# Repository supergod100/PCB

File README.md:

# KiCADでPCB作成
- main: PCB基板を作成するためのフォルダ・ファイル。完成形になるもの
- symbols: nRF52840_BLE_MCUの回路図等
- footprints: nRF52840_BLE_MCUのフットプリント

# フォルダ構成
```
Documents/KiCad/9.0/
    ├── footprints
    │   └── Original.pretty
    │       └── nRF52840_BLE_MCU.kicad_mod
    ├── main
    │   ├── fp-info-cache
    │   ├── main
    │   ├── main.kicad_pcb
    │   ├── main.kicad_prl
    │   ├── main.kicad_pro
    │   └── main.kicad_sch
    └── symbols
        ├── Original.bak
        └── Original.kicad_sym
```

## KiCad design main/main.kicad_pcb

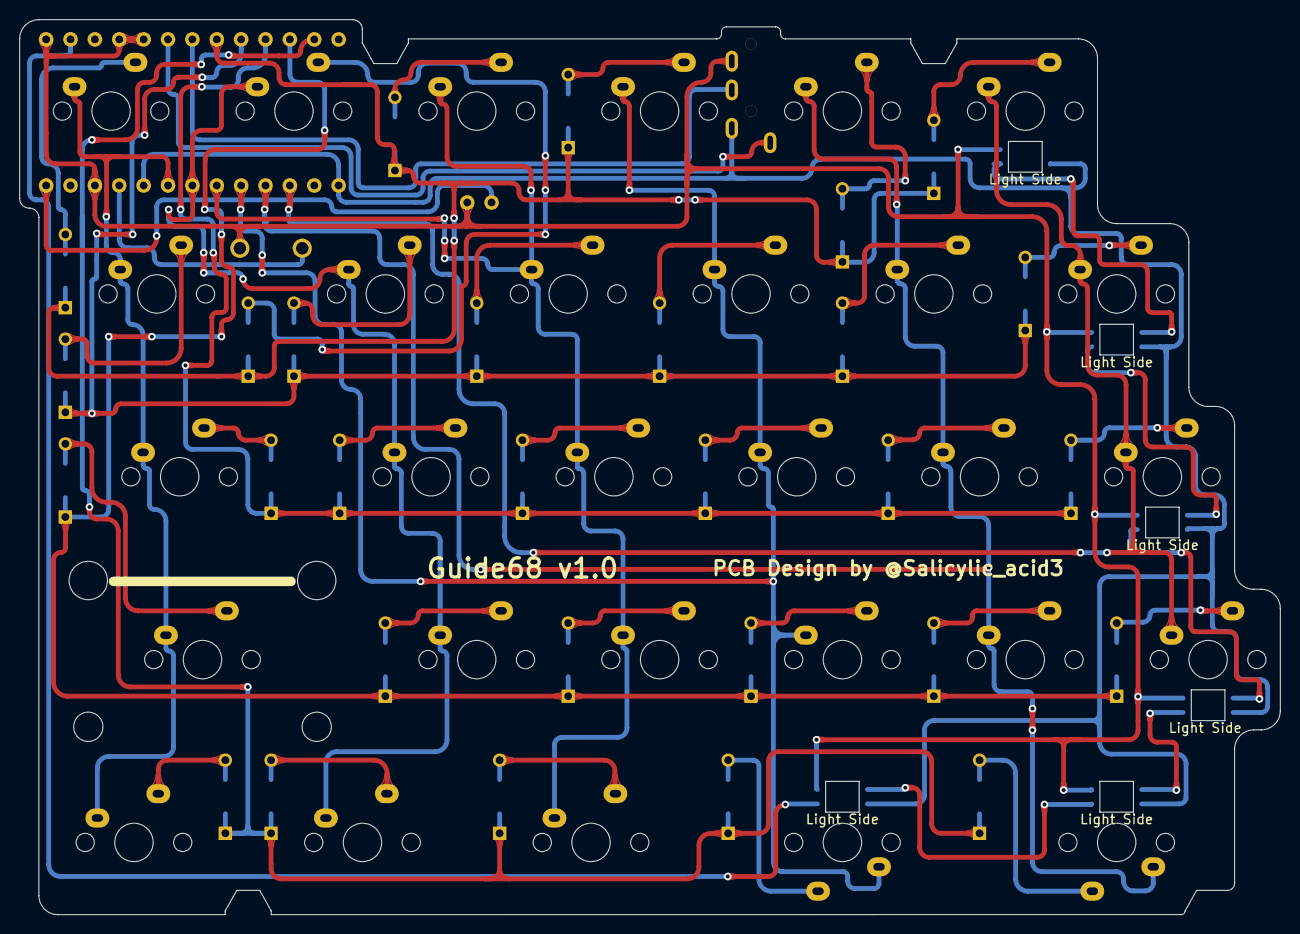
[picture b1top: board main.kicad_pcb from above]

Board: 2 copper layers, 131.3 x 93.2 mm, 68 parts (1 on the bottom side), 52 nets.

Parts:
D1, D2, D3, D4, D5, D6, D7, D8, D9, D10, D11, D12, D13, D14, D15, D16, D17, D18, D19, D20, D21, D22, D23, D24, D25, D26, D27, D28, D29: D; Diode_TH_SMD
J1: MJ-4PP-9; TRRS_MJ-4PP-9
J2: Conn_01x02; Battery_BMP_2pin
L1, L2, L3, L4, L5, L6: SK6812MINI; LED_SK6812MINI-E_BL
SW1, SW6, SW7, SW8, SW9, SW11, SW12, SW13, SW14, SW16, SW17, SW18, SW19, SW21, SW22, SW23, SW24, SW26, SW27, SW28, SW29: SW_PUSH; CherryMX_Solder_1u
SW2, SW20, SW25: SW_PUSH; CherryMX_Solder_1.5u
SW3: SW_PUSH; CherryMX_Solder_1.75u
SW4: SW_PUSH; CherryMX_Solder_2u_Rev
SW5, SW10, SW15: SW_PUSH; CherryMX_Solder_1.25u
SW30: SW_PUSH; ResetSW
U1: BLEMicroPro; Micon_BMP_7sKB

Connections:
Bat+: J2.1, U1.25 (BAT+)
Col0: SW1.1, SW2.1, SW3.1, SW4.1, SW5.1, U1.20 (F4/PIN20)
Col1: SW6.1, SW7.1, SW8.1, SW9.1, SW10.1, U1.19 (F5/PIN19)
Col2: SW11.1, SW12.1, SW13.1, SW14.1, SW15.1, U1.18 (F6/PIN18)
Col3: SW16.1, SW17.1, SW18.1, SW19.1, SW20.1, U1.17 (F7/PIN17)
Col4: SW21.1, SW22.1, SW23.1, SW24.1, SW25.1, U1.16 (B1/PIN16)
Col5: SW26.1, SW27.1, SW28.1, SW29.1, U1.15 (B3/PIN15)
Data_SCL: J1.C, U1.6 (D0/PIN6/SCL)
GND: J1.B, J2.2, L1.2 (VSS), L2.2 (VSS), L3.2 (VSS), L4.2 (VSS), L5.2 (VSS), L6.2 (VSS), SW30.2, U1.3 (GND), U1.4 (GND), U1.23 (GND), U1.26 (BAT-)
LED: L1.3 (DIN), U1.1 (D3/PIN1)
unnamed: D1.2 (A), SW1.2
unnamed: D2.2 (A), SW2.2
unnamed: D3.2 (A), SW3.2
unnamed: D4.2 (A), SW4.2
unnamed: D5.2 (A), SW5.2
unnamed: D6.2 (A), SW6.2
unnamed: D7.2 (A), SW7.2
unnamed: D8.2 (A), SW8.2
unnamed: D9.2 (A), SW9.2
unnamed: D10.2 (A), SW10.2
unnamed: D11.2 (A), SW11.2
unnamed: D12.2 (A), SW12.2
unnamed: D13.2 (A), SW13.2
unnamed: D14.2 (A), SW14.2
unnamed: D15.2 (A), SW15.2
unnamed: D16.2 (A), SW16.2
unnamed: D17.2 (A), SW17.2
unnamed: D18.2 (A), SW18.2
unnamed: D19.2 (A), SW19.2
unnamed: D20.2 (A), SW20.2
unnamed: D21.2 (A), SW21.2
unnamed: D22.2 (A), SW22.2
unnamed: D23.2 (A), SW23.2
unnamed: D24.2 (A), SW24.2
unnamed: D25.2 (A), SW25.2
unnamed: D26.2 (A), SW26.2
unnamed: D27.2 (A), SW27.2
unnamed: D28.2 (A), SW28.2
unnamed: D29.2 (A), SW29.2
unnamed: L1.1 (DOUT), L2.3 (DIN)
unnamed: L2.1 (DOUT), L3.3 (DIN)
unnamed: L3.1 (DOUT), L4.3 (DIN)
unnamed: L4.1 (DOUT), L5.3 (DIN)
unnamed: L5.1 (DOUT), L6.3 (DIN)
Reset: SW30.1, U1.22 (RST)
Row0: D1.1 (K), D6.1 (K), D11.1 (K), D16.1 (K), D21.1 (K), D26.1 (K), U1.7 (D4/PIN7)
Row1: D2.1 (K), D7.1 (K), D12.1 (K), D17.1 (K), D22.1 (K), D27.1 (K), U1.8 (C6/PIN8)
Row2: D3.1 (K), D8.1 (K), D13.1 (K), D18.1 (K), D23.1 (K), D28.1 (K), U1.9 (D7/PIN9)
Row3: D4.1 (K), D9.1 (K), D14.1 (K), D19.1 (K), D24.1 (K), D29.1 (K), U1.10 (E6/PIN10)
Row4: D5.1 (K), D10.1 (K), D15.1 (K), D20.1 (K), D25.1 (K), U1.11 (B4/PIN11)
SDA: J1.A, U1.5 (D1/PIN5/SDA)
VCC: J1.D, L1.4 (VDD), L2.4 (VDD), L3.4 (VDD), L4.4 (VDD), L5.4 (VDD), L6.4 (VDD), U1.13 (B6/PIN13), U1.21 (VCC)

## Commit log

2026-02-10 first
2026-02-10 READ.mdを追加
2026-02-10 readme変更
2026-02-10 readme変更2
2026-02-10 readme変更3
2026-02-11 マイコンのシンボルとフットプリント完成？ 次はマイコンとフットプリントの回路図を作成
